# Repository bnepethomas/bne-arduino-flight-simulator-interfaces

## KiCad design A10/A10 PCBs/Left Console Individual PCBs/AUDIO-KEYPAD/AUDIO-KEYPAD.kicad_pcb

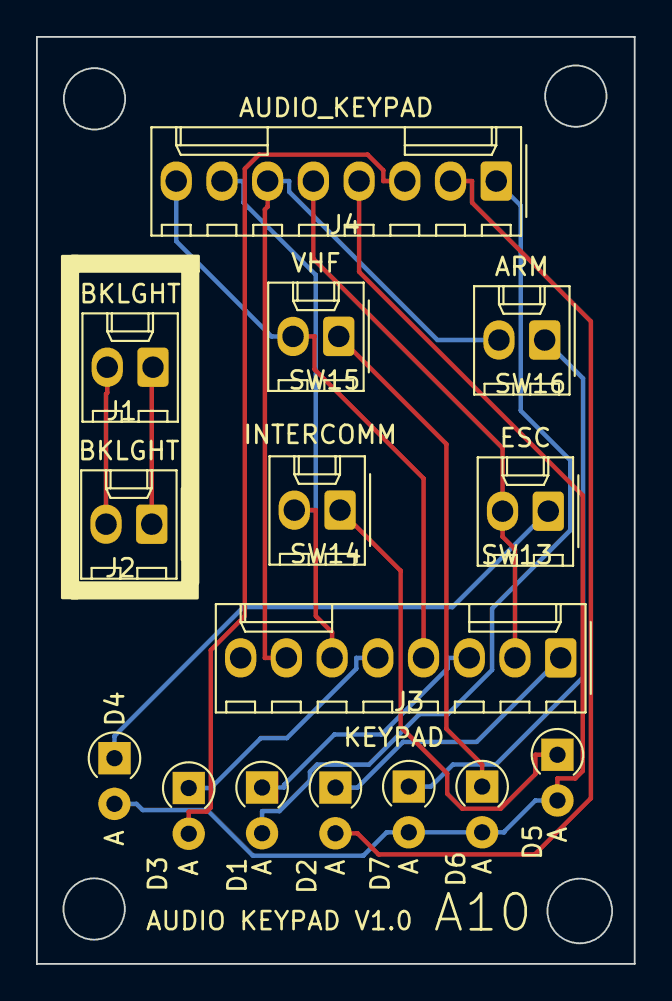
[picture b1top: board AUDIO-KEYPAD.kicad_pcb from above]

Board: 2 copper layers, 33.2 x 51.5 mm, 15 parts (0 on the bottom side), 17 nets.

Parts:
D1, D2, D3, D4, D5, D6, D7: D; D_A-405_P2.54mm_Vertical_AnodeUp
J1, J2: BKLGHT; Molex_KK-254_AE-6410-02A_1x02_P2.54mm_Vertical
J3: KEYPAD; Molex_KK-254_AE-6410-08A_1x08_P2.54mm_Vertical
J4: AUDIO_KEYPAD; Molex_KK-254_AE-6410-08A_1x08_P2.54mm_Vertical
SW13: ESC; Molex_KK-254_AE-6410-02A_1x02_P2.54mm_Vertical
SW14: INTERCOMM; Molex_KK-254_AE-6410-02A_1x02_P2.54mm_Vertical
SW15: VHF; Molex_KK-254_AE-6410-02A_1x02_P2.54mm_Vertical
SW16: ARM; Molex_KK-254_AE-6410-02A_1x02_P2.54mm_Vertical

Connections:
/COL0: D1.2 (A), J4.1
/COL0_POSTDIODE: D1.1 (K), J3.3
/COL1: D2.2 (A), J4.2
/COL1_POSTDIODE: D2.1 (K), J3.1
/COL2: D3.2 (A), J4.3
/COL2_POSTDIODE: D3.1 (K), J3.5
/COL3: D4.2 (A), D5.2 (A), D6.2 (A), D7.2 (A), J4.4
/ROW0: J3.2, J4.5, SW13.2
/ROW1: J3.7, J4.6, SW16.2
/ROW2: J3.6, J4.7, SW14.2
/ROW3: J3.4, J4.8, SW15.2
unnamed: D4.1 (K), SW13.1
unnamed: D5.1 (K), SW14.1
unnamed: D6.1 (K), SW15.1
unnamed: D7.1 (K), SW16.1
unnamed: J1.1, J2.1
unnamed: J1.2, J2.2

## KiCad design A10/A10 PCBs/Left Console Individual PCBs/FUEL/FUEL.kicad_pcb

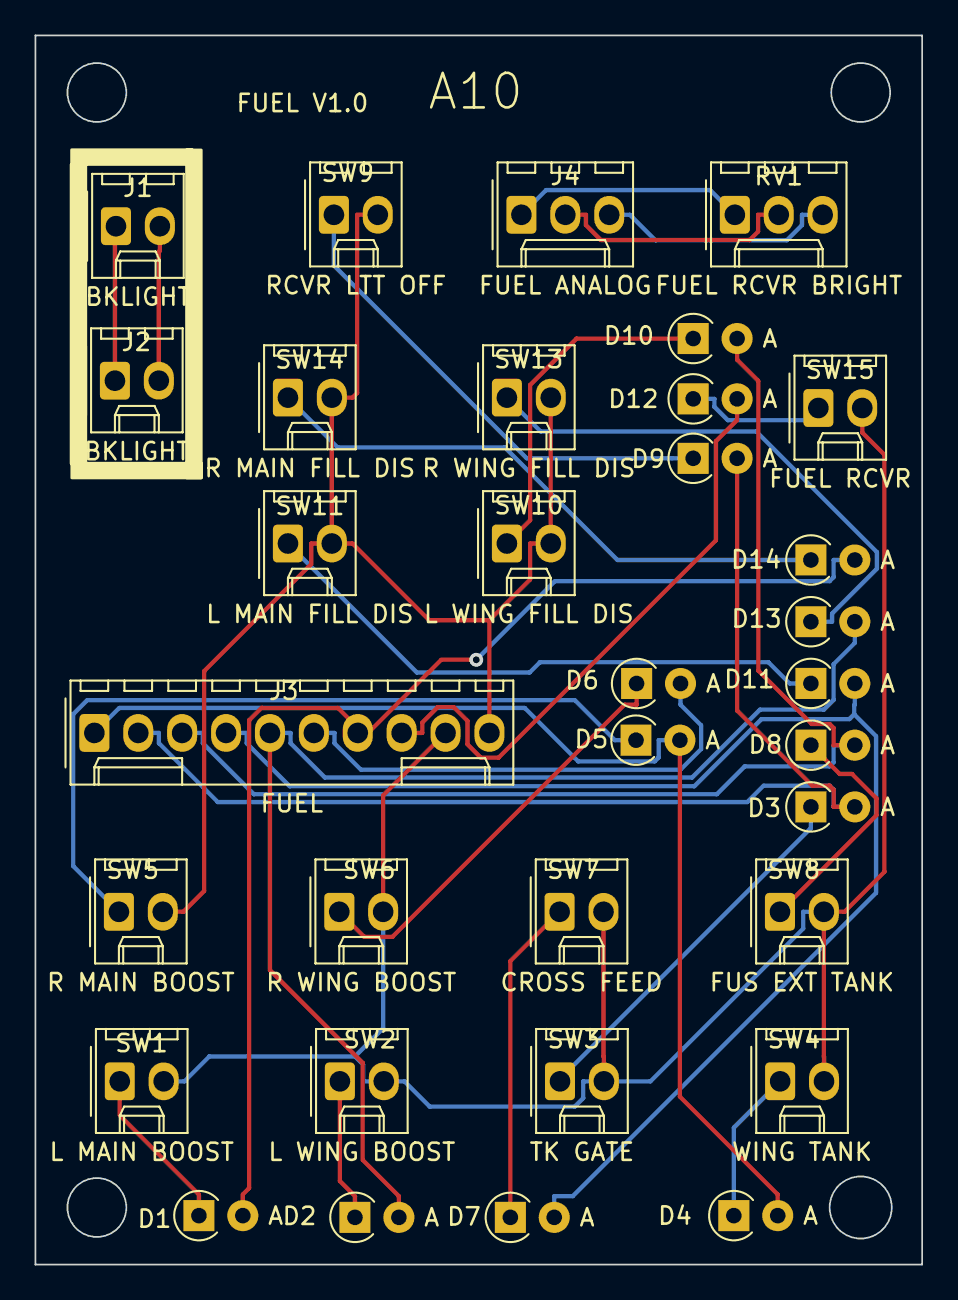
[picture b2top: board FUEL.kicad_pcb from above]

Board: 2 copper layers, 51.3 x 71.1 mm, 33 parts (0 on the bottom side), 29 nets.

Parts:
D1, D2, D3, D4, D5, D6, D7, D8, D9, D10, D11, D12, D13, D14: D; D_A-405_P2.54mm_Vertical_AnodeUp
J1, J2: BKLIGHT; Molex_KK-254_AE-6410-02A_1x02_P2.54mm_Vertical
J3: FUEL; Molex_KK-254_AE-6410-10A_1x10_P2.54mm_Vertical
J4: FUEL ANALOG; Molex_KK-254_AE-6410-03A_1x03_P2.54mm_Vertical
RV1: FUEL RCVR BRIGHT; Molex_KK-254_AE-6410-03A_1x03_P2.54mm_Vertical
SW1: L MAIN BOOST; Molex_KK-254_AE-6410-02A_1x02_P2.54mm_Vertical
SW2: L WING BOOST; Molex_KK-254_AE-6410-02A_1x02_P2.54mm_Vertical
SW3: TK GATE; Molex_KK-254_AE-6410-02A_1x02_P2.54mm_Vertical
SW4: WING TANK; Molex_KK-254_AE-6410-02A_1x02_P2.54mm_Vertical
SW5: R MAIN BOOST; Molex_KK-254_AE-6410-02A_1x02_P2.54mm_Vertical
SW6: R WING BOOST; Molex_KK-254_AE-6410-02A_1x02_P2.54mm_Vertical
SW7: CROSS FEED; Molex_KK-254_AE-6410-02A_1x02_P2.54mm_Vertical
SW8: FUS EXT TANK; Molex_KK-254_AE-6410-02A_1x02_P2.54mm_Vertical
SW9: RCVR LTT OFF; Molex_KK-254_AE-6410-02A_1x02_P2.54mm_Vertical
SW10: L WING FILL DIS; Molex_KK-254_AE-6410-02A_1x02_P2.54mm_Vertical
SW11: L MAIN FILL DIS; Molex_KK-254_AE-6410-02A_1x02_P2.54mm_Vertical
SW13: R WING FILL DIS; Molex_KK-254_AE-6410-02A_1x02_P2.54mm_Vertical
SW14: R MAIN FILL DIS; Molex_KK-254_AE-6410-02A_1x02_P2.54mm_Vertical
SW15: FUEL RCVR; Molex_KK-254_AE-6410-02A_1x02_P2.54mm_Vertical

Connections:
/ANALOG_5V: J4.1, RV1.1
/ANALOG_GND: J4.3, RV1.3
/COL0: D4.2 (A), D5.2 (A), J3.1
/COL1: D3.2 (A), D9.2 (A), J3.2
/COL2: D8.2 (A), D10.2 (A), J3.3
/COL3: D7.2 (A), D11.2 (A), J3.4
/COL4: D2.2 (A), D13.2 (A), J3.5
/COL5: D6.2 (A), J3.6
/COL6: D1.2 (A), D14.2 (A), J3.7
/COL7: D12.2 (A), J3.8
/RCVR_BRIGHT: J4.2, RV1.2
/ROW5: J3.9, SW1.2 (B), SW2.2 (B), SW3.2 (B), SW4.2 (B), SW6.2 (B), SW7.2 (B), SW8.2 (B), SW15.2 (B)
/ROW6: J3.10, SW5.2 (B), SW9.2 (B), SW10.2, SW11.2, SW13.2, SW14.2
unnamed: D1.1 (K), SW1.1 (A)
unnamed: D2.1 (K), SW2.1 (A)
unnamed: D3.1 (K), SW3.1 (A)
unnamed: D4.1 (K), SW4.1 (A)
unnamed: D5.1 (K), SW5.1 (A)
unnamed: D6.1 (K), SW6.1 (A)
unnamed: D7.1 (K), SW7.1 (A)
unnamed: D8.1 (K), SW8.1 (A)
unnamed: D9.1 (K), SW9.1 (A)
unnamed: D10.1 (K), SW10.1
unnamed: D11.1 (K), SW11.1
unnamed: D12.1 (K), SW15.1 (A)
unnamed: D13.1 (K), SW13.1
unnamed: D14.1 (K), SW14.1
unnamed: J1.1, J2.1
unnamed: J1.2, J2.2

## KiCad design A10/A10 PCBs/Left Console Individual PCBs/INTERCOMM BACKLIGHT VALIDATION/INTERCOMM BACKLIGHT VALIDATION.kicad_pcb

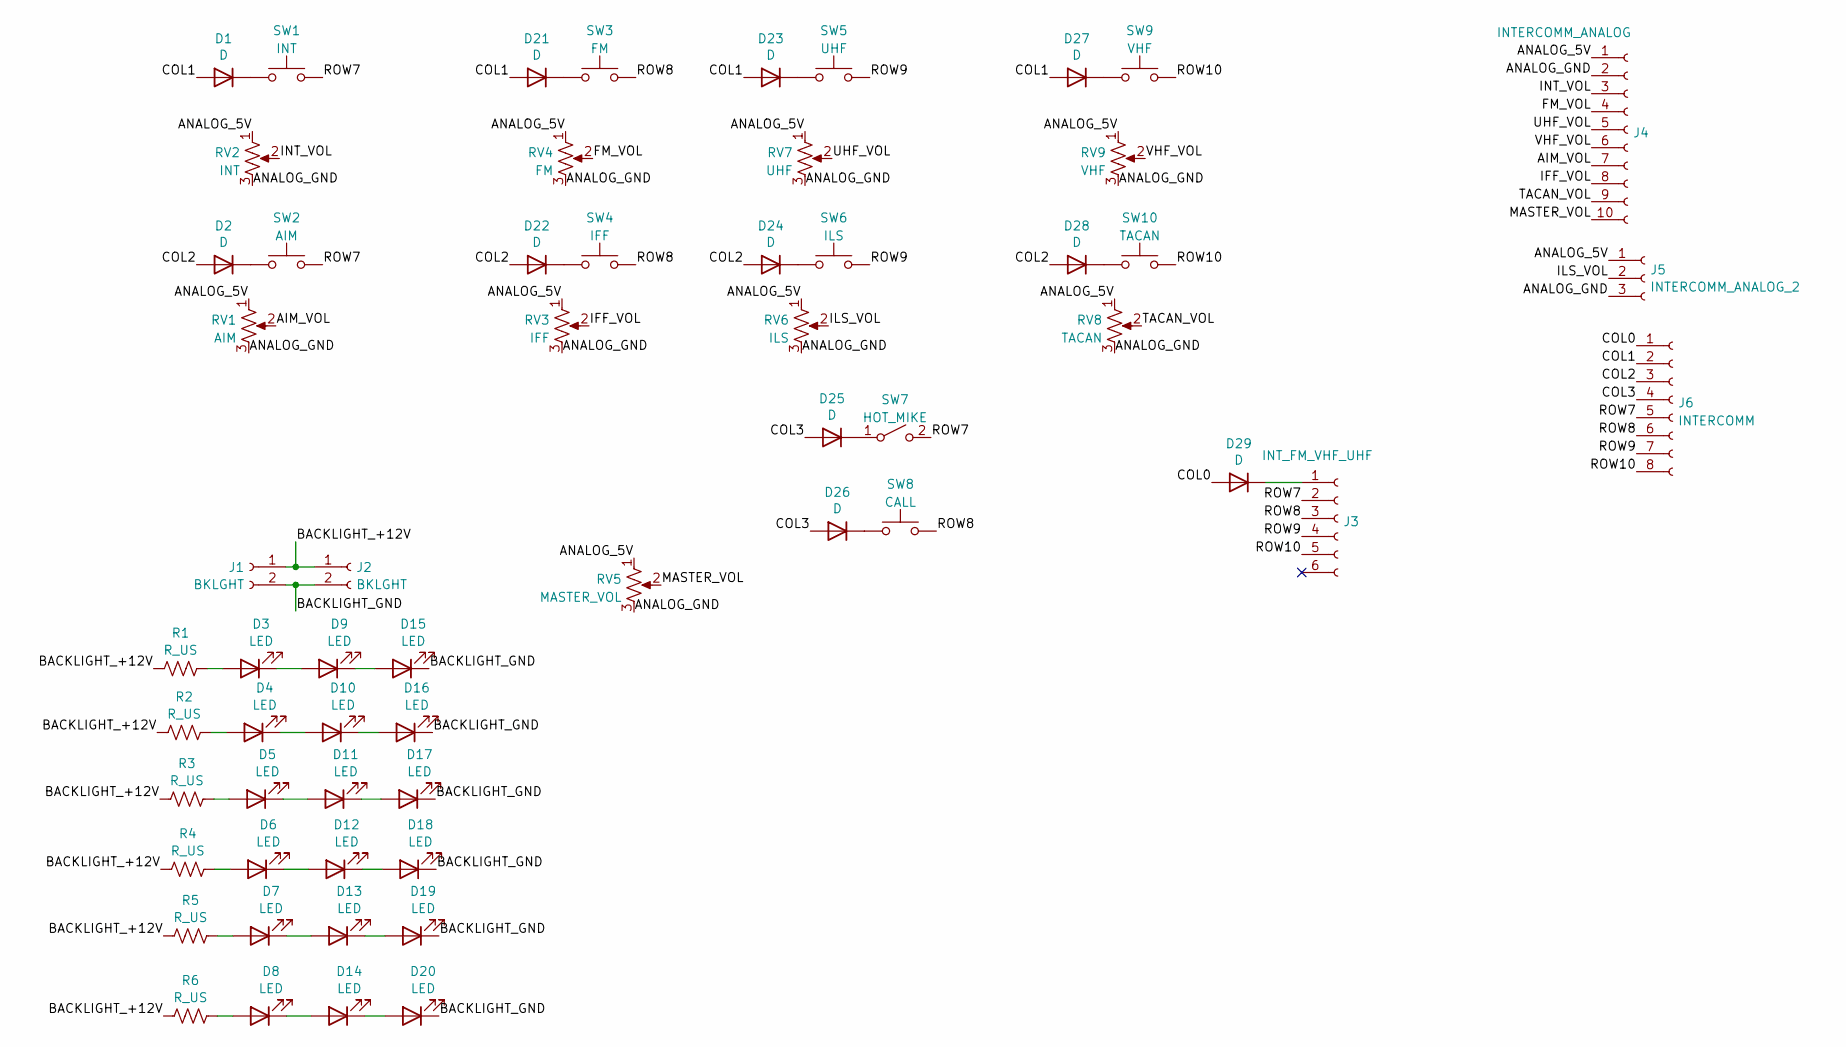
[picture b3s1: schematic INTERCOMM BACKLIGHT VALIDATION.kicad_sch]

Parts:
D1, D2, D21, D22, D23, D24, D25, D26, D27, D28, D29: D; D_A-405_P2.54mm_Vertical_AnodeUp
D3, D4, D5, D6, D7, D8, D9, D10, D11, D12, D13, D14, D15, D16, D17, D18, D19, D20: LED; LED_D3.0mm_FlatTop
J1, J2: BKLGHT; Molex_KK-254_AE-6410-02A_1x02_P2.54mm_Vertical
J3: INT_FM_VHF_UHF; Molex_KK-254_AE-6410-06A_1x06_P2.54mm_Vertical
J4: INTERCOMM_ANALOG; Molex_KK-254_AE-6410-10A_1x10_P2.54mm_Vertical
J5: INTERCOMM_ANALOG_2; Molex_KK-254_AE-6410-03A_1x03_P2.54mm_Vertical
J6: INTERCOMM; Molex_KK-254_AE-6410-08A_1x08_P2.54mm_Vertical
R1, R2, R3, R4, R5, R6: R_US; R_Axial_DIN0207_L6.3mm_D2.5mm_P2.54mm_Vertical
RV1: AIM; Molex_KK-254_AE-6410-03A_1x03_P2.54mm_Vertical
RV2: INT; Molex_KK-254_AE-6410-03A_1x03_P2.54mm_Vertical
RV3: IFF; Molex_KK-254_AE-6410-03A_1x03_P2.54mm_Vertical
RV4: FM; Molex_KK-254_AE-6410-03A_1x03_P2.54mm_Vertical
RV5: MASTER_VOL; Molex_KK-254_AE-6410-03A_1x03_P2.54mm_Vertical
RV6: ILS; Molex_KK-254_AE-6410-03A_1x03_P2.54mm_Vertical
RV7: UHF; Molex_KK-254_AE-6410-03A_1x03_P2.54mm_Vertical
RV8: TACAN; Molex_KK-254_AE-6410-03A_1x03_P2.54mm_Vertical
RV9: VHF; Molex_KK-254_AE-6410-03A_1x03_P2.54mm_Vertical
SW1: INT; Molex_KK-254_AE-6410-02A_1x02_P2.54mm_Vertical
SW2: AIM; Molex_KK-254_AE-6410-02A_1x02_P2.54mm_Vertical
SW3: FM; Molex_KK-254_AE-6410-02A_1x02_P2.54mm_Vertical
SW4: IFF; Molex_KK-254_AE-6410-02A_1x02_P2.54mm_Vertical
SW5: UHF; Molex_KK-254_AE-6410-02A_1x02_P2.54mm_Vertical
SW6: ILS; Molex_KK-254_AE-6410-02A_1x02_P2.54mm_Vertical
SW7: HOT_MIKE; Molex_KK-254_AE-6410-02A_1x02_P2.54mm_Vertical
SW8: CALL; Molex_KK-254_AE-6410-02A_1x02_P2.54mm_Vertical
SW9: VHF; Molex_KK-254_AE-6410-02A_1x02_P2.54mm_Vertical
SW10: TACAN; Molex_KK-254_AE-6410-02A_1x02_P2.54mm_Vertical

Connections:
/AIM_VOL: J4.7, RV1.2
/ANALOG_5V: J4.1, J5.1, RV1.1, RV2.1, RV3.1, RV4.1, RV5.1, RV6.1, RV7.1, RV8.1, RV9.1
/ANALOG_GND: J4.2, J5.3, RV1.3, RV2.3, RV3.3, RV4.3, RV5.3, RV6.3, RV7.3, RV8.3, RV9.3
/BACKLIGHT_+12V: J1.1, J2.1, R1.1, R2.1, R3.1, R4.1, R5.1, R6.1
/BACKLIGHT_GND: D15.1 (K), D16.1 (K), D17.1 (K), D18.1 (K), D19.1 (K), D20.1 (K), J1.2, J2.2
/COL0: D29.2 (A), J6.1
/COL1: D1.2 (A), D21.2 (A), D23.2 (A), D27.2 (A), J6.2
/COL2: D2.2 (A), D22.2 (A), D24.2 (A), D28.2 (A), J6.3
/COL3: D25.2 (A), D26.2 (A), J6.4
/FM_VOL: J4.4, RV4.2
/IFF_VOL: J4.8, RV3.2
/ILS_VOL: J5.2, RV6.2
/INT_VOL: J4.3, RV2.2
/MASTER_VOL: J4.10, RV5.2
/ROW7: J3.2, J6.5, SW1.2, SW2.2, SW7.2 (B)
/ROW8: J3.3, J6.6, SW3.2, SW4.2, SW8.2
/ROW9: J3.4, J6.7, SW5.2, SW6.2
/ROW10: J3.5, J6.8, SW9.2, SW10.2
/TACAN_VOL: J4.9, RV8.2
/UHF_VOL: J4.5, RV7.2
/VHF_VOL: J4.6, RV9.2
unnamed: D1.1 (K), SW1.1
unnamed: D2.1 (K), SW2.1
unnamed: D3.2 (A), R1.2
unnamed: D3.1 (K), D9.2 (A)
unnamed: D4.2 (A), R2.2
unnamed: D5.2 (A), R3.2
unnamed: D6.2 (A), R4.2
unnamed: D7.2 (A), R5.2
unnamed: D8.2 (A), R6.2
unnamed: D4.1 (K), D10.2 (A)
unnamed: D10.1 (K), D16.2 (A)
unnamed: D5.1 (K), D11.2 (A)
unnamed: D11.1 (K), D17.2 (A)
unnamed: D6.1 (K), D12.2 (A)
unnamed: D12.1 (K), D18.2 (A)
unnamed: D7.1 (K), D13.2 (A)
unnamed: D13.1 (K), D19.2 (A)
unnamed: D8.1 (K), D14.2 (A)
unnamed: D14.1 (K), D20.2 (A)
unnamed: D9.1 (K), D15.2 (A)
unnamed: D21.1 (K), SW3.1
unnamed: D22.1 (K), SW4.1
unnamed: D23.1 (K), SW5.1
unnamed: D24.1 (K), SW6.1
unnamed: D25.1 (K), SW7.1 (A)
unnamed: D26.1 (K), SW8.1
unnamed: D27.1 (K), SW9.1
unnamed: D28.1 (K), SW10.1
unnamed: D29.1 (K), J3.1

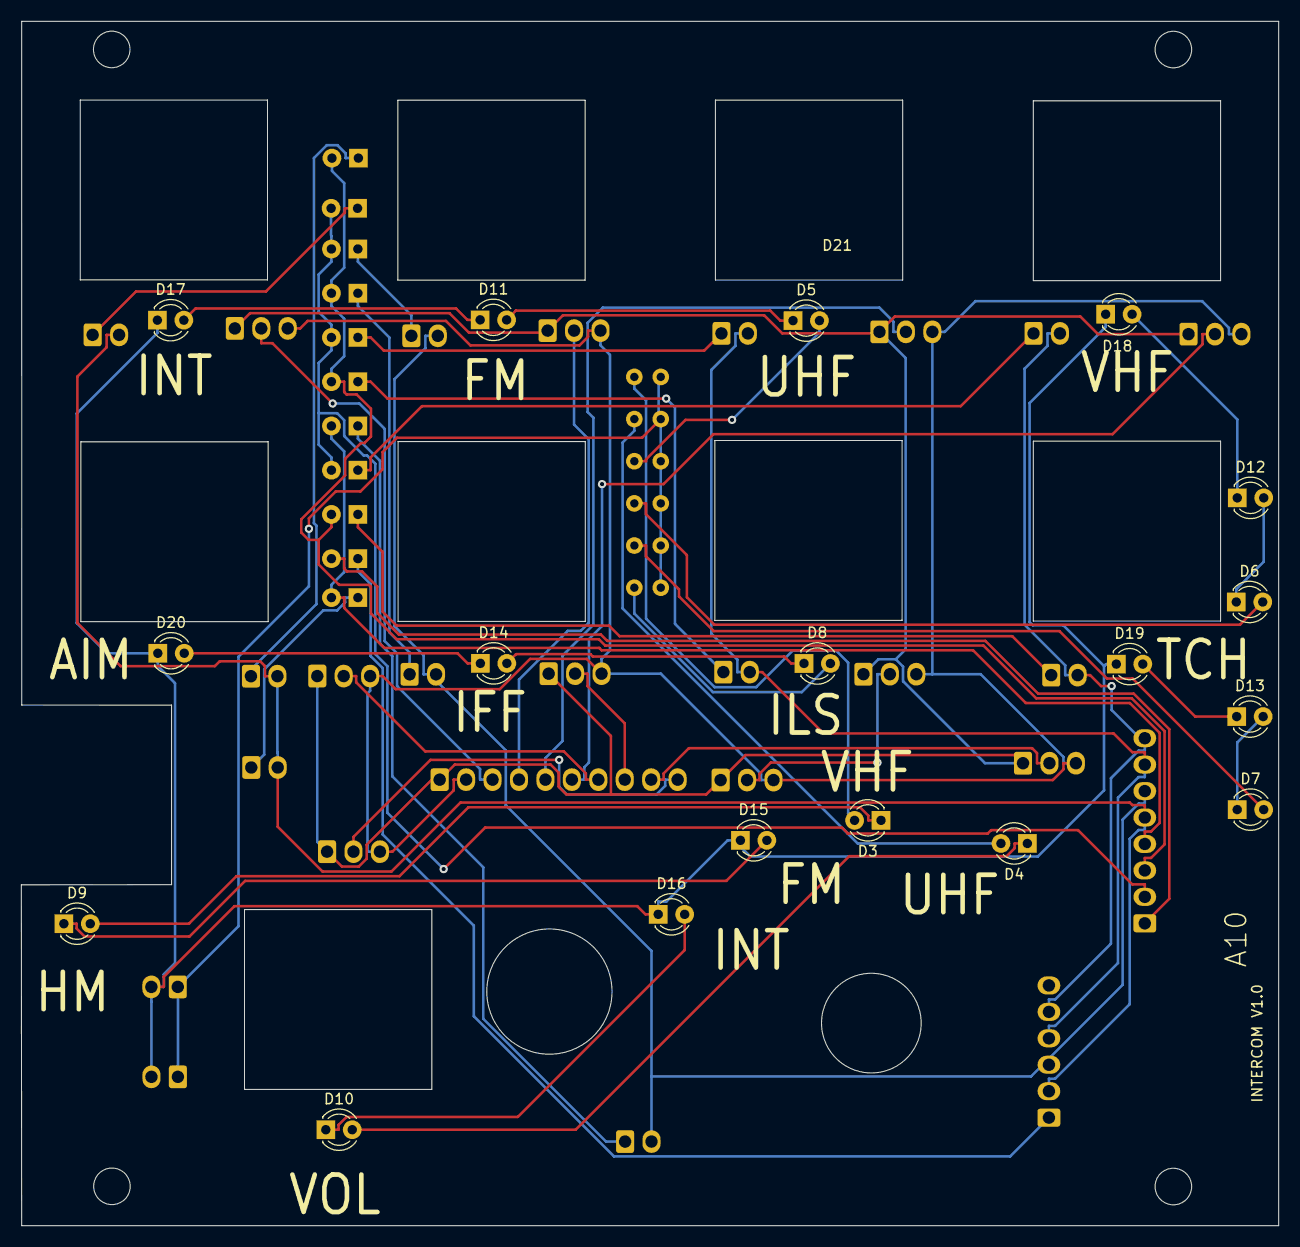
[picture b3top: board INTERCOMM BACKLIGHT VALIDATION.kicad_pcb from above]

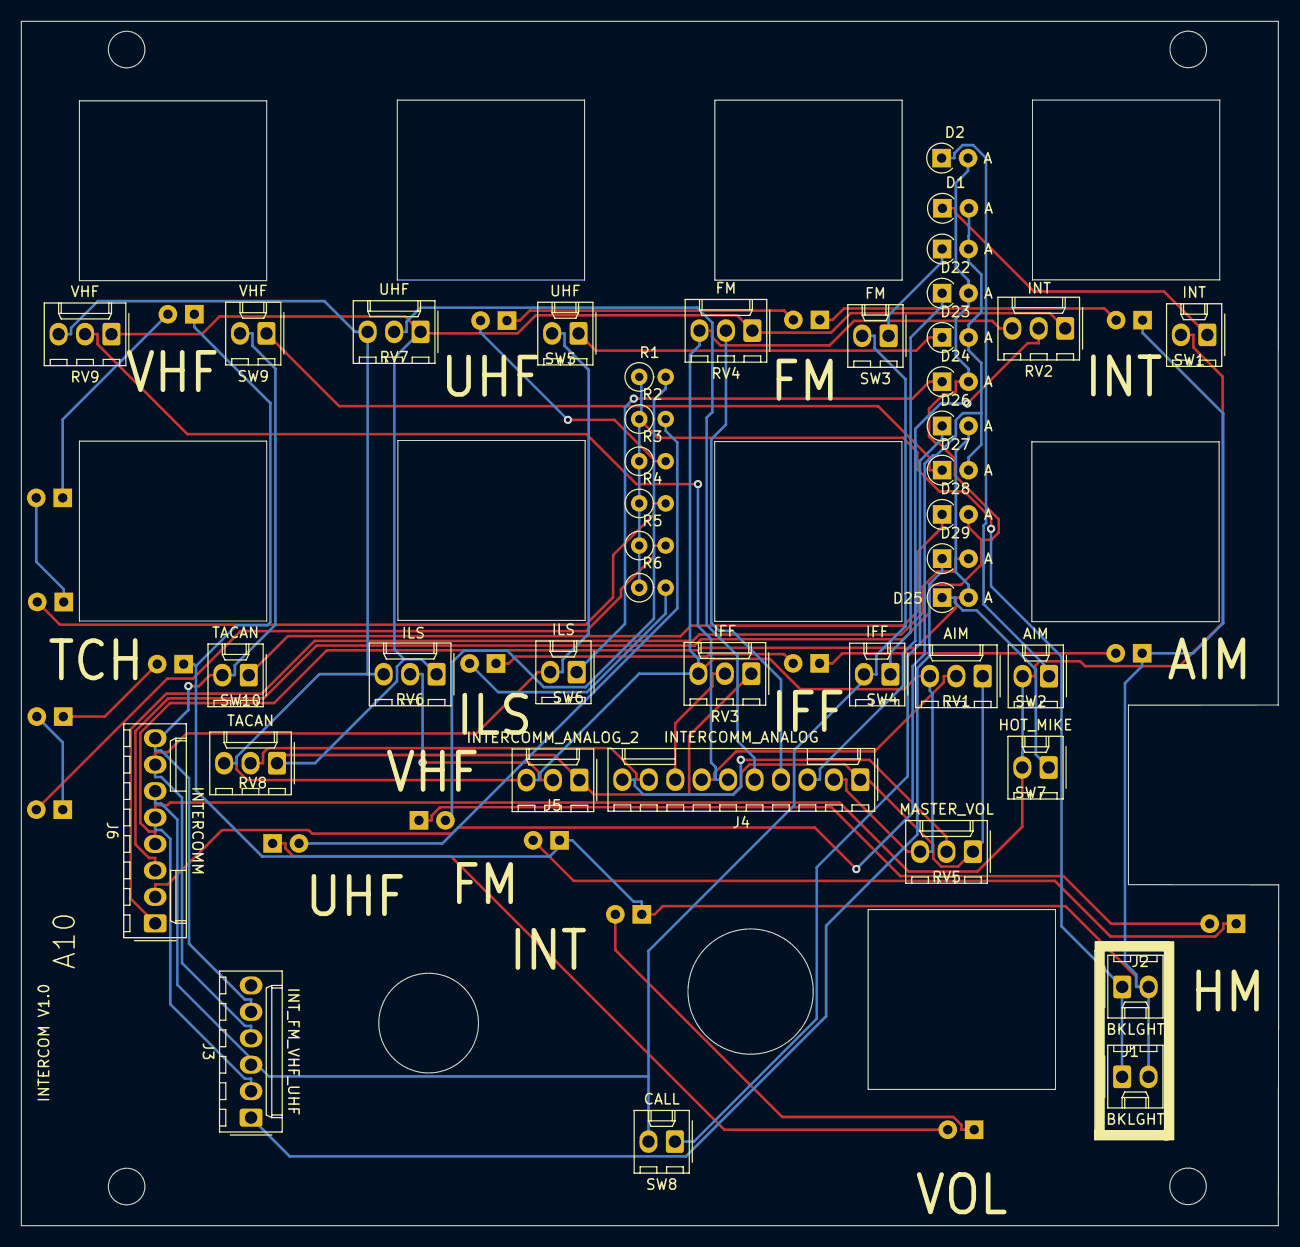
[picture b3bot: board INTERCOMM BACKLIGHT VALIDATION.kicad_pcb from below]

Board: 2 copper layers, 120.8 x 115.7 mm, 60 parts (42 on the bottom side), 50 nets.

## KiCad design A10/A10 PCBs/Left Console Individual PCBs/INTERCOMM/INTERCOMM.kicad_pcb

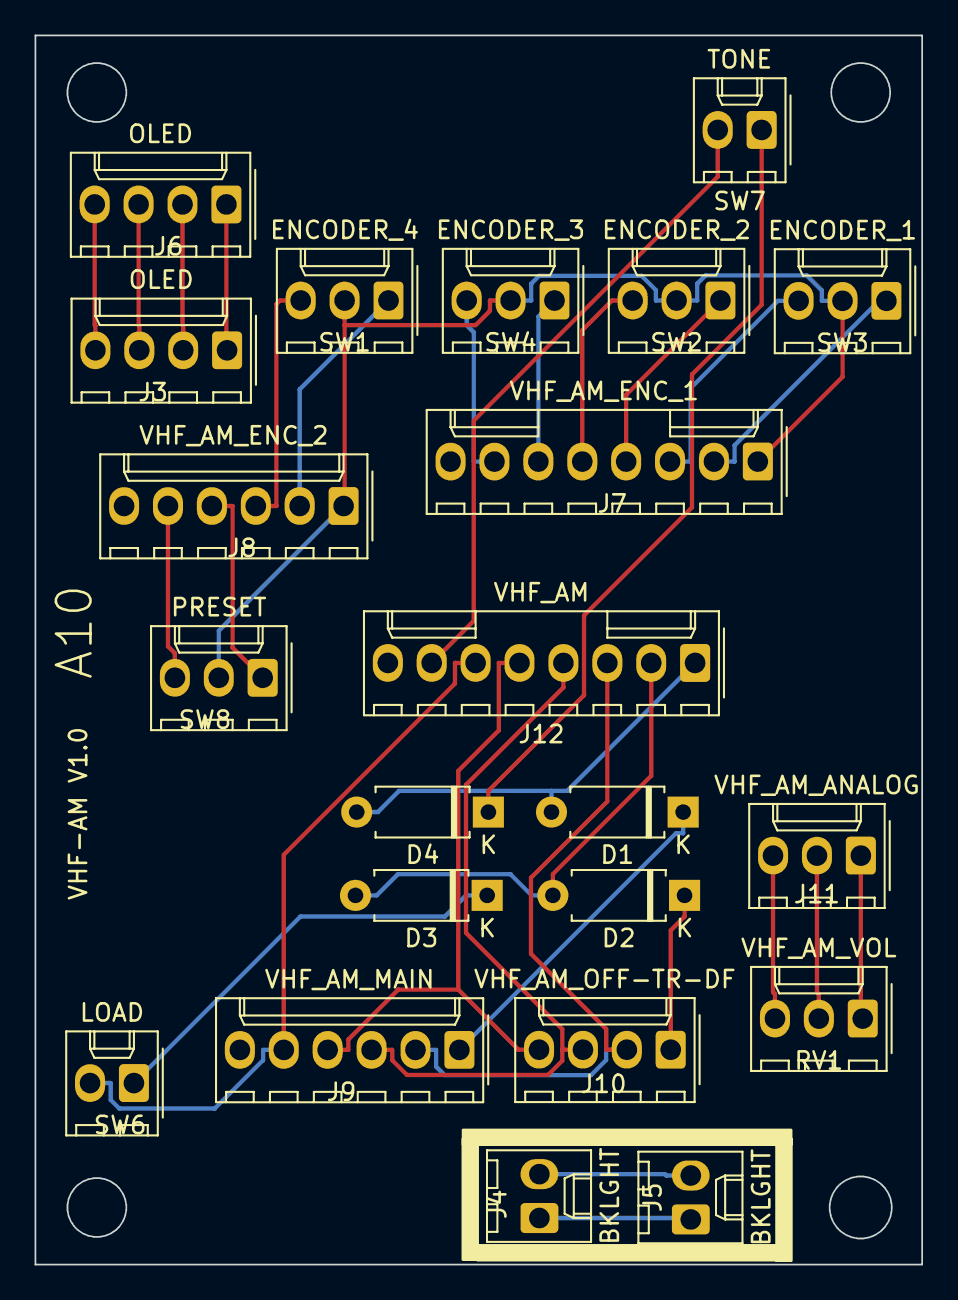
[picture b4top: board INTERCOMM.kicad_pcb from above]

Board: 2 copper layers, 51.3 x 71.1 mm, 22 parts (0 on the bottom side), 31 nets.

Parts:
D1, D2, D3, D4: D; D_A-405_P7.62mm_Horizontal
J3, J6: OLED; Molex_KK-254_AE-6410-04A_1x04_P2.54mm_Vertical
J4, J5: BKLGHT; Molex_KK-254_AE-6410-02A_1x02_P2.54mm_Vertical
J7: VHF_AM_ENC_1; Molex_KK-254_AE-6410-08A_1x08_P2.54mm_Vertical
J8: VHF_AM_ENC_2; Molex_KK-254_AE-6410-06A_1x06_P2.54mm_Vertical
J9: VHF_AM_MAIN; Molex_KK-254_AE-6410-06A_1x06_P2.54mm_Vertical
J10: VHF_AM_OFF-TR-DF; Molex_KK-254_AE-6410-04A_1x04_P2.54mm_Vertical
J11: VHF_AM_ANALOG; Molex_KK-254_AE-6410-03A_1x03_P2.54mm_Vertical
J12: VHF_AM; Molex_KK-254_AE-6410-08A_1x08_P2.54mm_Vertical
RV1: VHF_AM_VOL; Molex_KK-254_AE-6410-03A_1x03_P2.54mm_Vertical
SW1: ENCODER_4; Molex_KK-254_AE-6410-03A_1x03_P2.54mm_Vertical
SW2: ENCODER_2; Molex_KK-254_AE-6410-03A_1x03_P2.54mm_Vertical
SW3: ENCODER_1; Molex_KK-254_AE-6410-03A_1x03_P2.54mm_Vertical
SW4: ENCODER_3; Molex_KK-254_AE-6410-03A_1x03_P2.54mm_Vertical
SW6: LOAD; Molex_KK-254_AE-6410-02A_1x02_P2.54mm_Vertical
SW7: TONE; Molex_KK-254_AE-6410-02A_1x02_P2.54mm_Vertical
SW8: PRESET; Molex_KK-254_AE-6410-03A_1x03_P2.54mm_Vertical

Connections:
/ANALOG_5V: J11.1, RV1.1
/ANALOG_GND: J11.3, RV1.3
/COL4: D1.2 (A), D4.2 (A), J12.1
/COL5: D2.2 (A), D3.2 (A), J12.2
/ROW0: J9.2, J10.2, J12.3
/ROW1: J9.3, J10.3, J12.4
/ROW2: J9.4, J10.4, J12.5
/ROW3: J9.5, J12.6, SW6.2
/ROW4: J12.7, SW7.2
/VHF_AM_VOL: J11.2, RV1.2
/VHF__AM_ENC_1_A: J7.2, SW3.1
/VHF__AM_ENC_1_B: J7.3, SW3.3
/VHF__AM_ENC_2_A: J7.4, SW2.1
/VHF__AM_ENC_2_B: J7.5, SW2.3
/VHF__AM_ENC_3_A: J7.6, SW4.1
/VHF__AM_ENC_3_B: J7.7, SW4.3
/VHF__AM_ENC_4_A: J8.2, SW1.1
/VHF__AM_ENC_4_B: J8.3, SW1.3
/VHF__AM_PRESET_A: J8.4, SW8.1
/VHF__AM_PRESET_B: J8.5, SW8.3
GND: J7.1, J8.1, SW1.2, SW2.2, SW3.2, SW4.2, SW8.2
unnamed: D1.1 (K), J9.1
unnamed: D2.1 (K), J10.1
unnamed: D3.1 (K), SW6.1
unnamed: D4.1 (K), SW7.1
unnamed: J3.1, J6.1
unnamed: J3.2, J6.2
unnamed: J3.3, J6.3
unnamed: J3.4, J6.4
unnamed: J4.1, J5.1
unnamed: J4.2, J5.2

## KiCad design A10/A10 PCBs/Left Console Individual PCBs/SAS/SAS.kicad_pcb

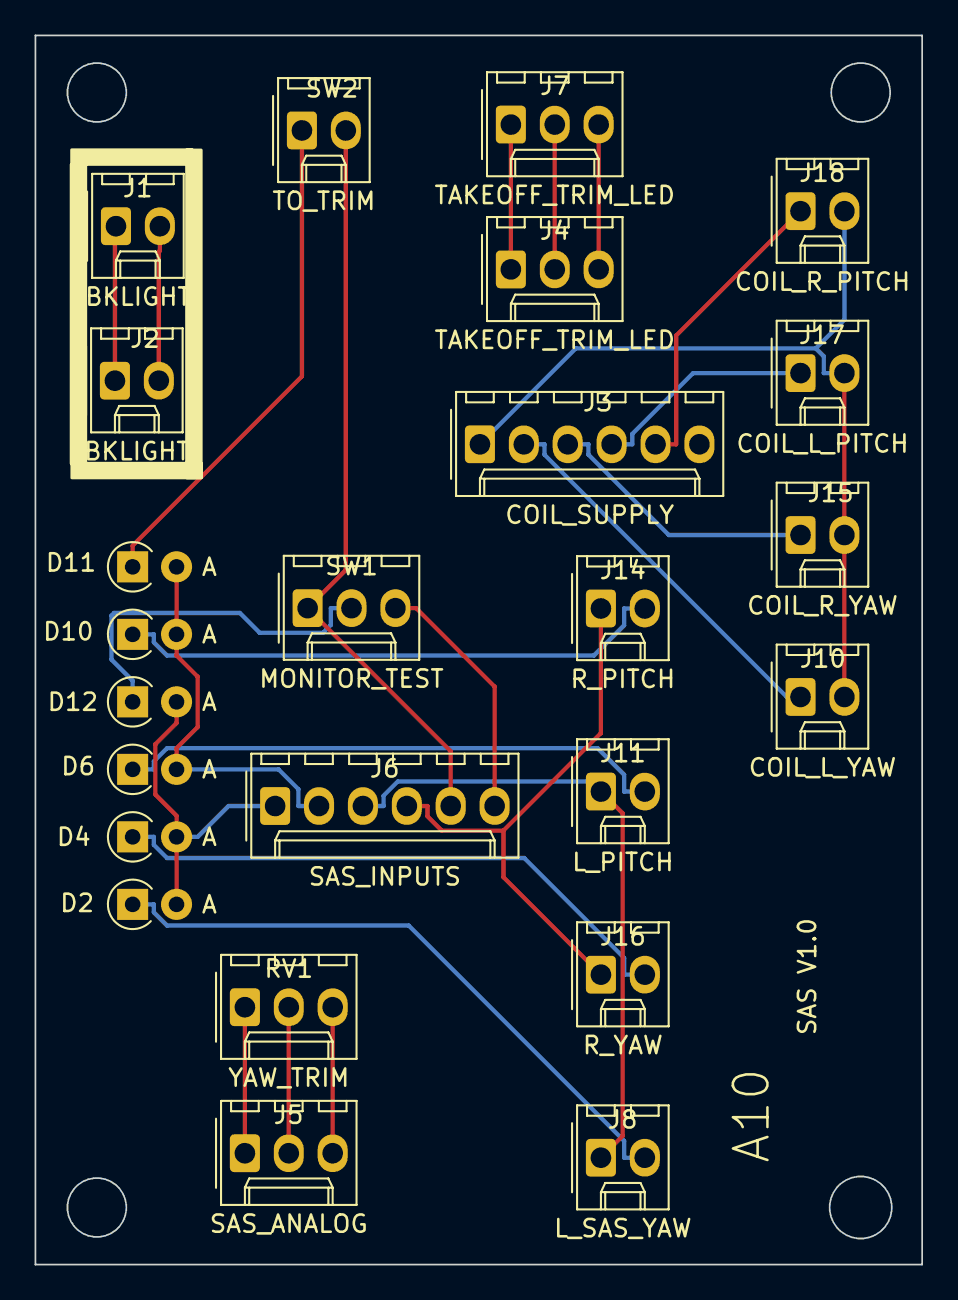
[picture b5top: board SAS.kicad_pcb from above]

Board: 2 copper layers, 51.3 x 71.1 mm, 24 parts (0 on the bottom side), 25 nets.

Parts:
D2, D4, D6, D10, D11, D12: D; D_A-405_P2.54mm_Vertical_AnodeUp
J1, J2: BKLIGHT; Molex_KK-254_AE-6410-02A_1x02_P2.54mm_Vertical
J3: COIL_SUPPLY; Molex_KK-254_AE-6410-06A_1x06_P2.54mm_Vertical
J4, J7: TAKEOFF_TRIM_LED; Molex_KK-254_AE-6410-03A_1x03_P2.54mm_Vertical
J5: SAS_ANALOG; Molex_KK-254_AE-6410-03A_1x03_P2.54mm_Vertical
J6: SAS_INPUTS; Molex_KK-254_AE-6410-06A_1x06_P2.54mm_Vertical
J8: L_SAS_YAW; Molex_KK-254_AE-6410-02A_1x02_P2.54mm_Vertical
J10: COIL_L_YAW; Molex_KK-254_AE-6410-02A_1x02_P2.54mm_Vertical
J11: L_PITCH; Molex_KK-254_AE-6410-02A_1x02_P2.54mm_Vertical
J14: R_PITCH; Molex_KK-254_AE-6410-02A_1x02_P2.54mm_Vertical
J15: COIL_R_YAW; Molex_KK-254_AE-6410-02A_1x02_P2.54mm_Vertical
J16: R_YAW; Molex_KK-254_AE-6410-02A_1x02_P2.54mm_Vertical
J17: COIL_L_PITCH; Molex_KK-254_AE-6410-02A_1x02_P2.54mm_Vertical
J18: COIL_R_PITCH; Molex_KK-254_AE-6410-02A_1x02_P2.54mm_Vertical
RV1: YAW_TRIM; Molex_KK-254_AE-6410-03A_1x03_P2.54mm_Vertical
SW1: MONITOR_TEST; Molex_KK-254_AE-6410-03A_1x03_P2.54mm_Vertical
SW2: TO_TRIM; Molex_KK-254_AE-6410-02A_1x02_P2.54mm_Vertical

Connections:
/ANALOG_5V: J5.1, RV1.1
/ANALOG_GND: J5.3, RV1.3
/COIL_28V: J3.1, J10.2, J15.2, J17.2, J18.2
/COIL_L_PITCH: J3.4, J17.1
/COIL_L_YAW: J3.2, J10.1
/COIL_R_PITCH: J3.5, J18.1
/COIL_R_YAW: J3.3, J15.1
/COL9: D2.2 (A), D4.2 (A), D12.2 (A), J6.1
/COL10: D6.2 (A), D10.2 (A), D11.2 (A), J6.2
/ROW0: J6.3, J8.1, J11.1
/ROW1: J6.4, J14.1, J16.1
/ROW2: J6.5, SW1.1, SW2.2
/ROW3: J6.6, SW1.3
/YAW_TRIM: J5.2, RV1.2
unnamed: D2.1 (K), J8.2
unnamed: D4.1 (K), J16.2
unnamed: D6.1 (K), J11.2
unnamed: D10.1 (K), J14.2
unnamed: D11.1 (K), SW2.1
unnamed: D12.1 (K), SW1.2
unnamed: J1.1, J2.1
unnamed: J1.2, J2.2
unnamed: J4.1, J7.1
unnamed: J4.2, J7.2
unnamed: J4.3, J7.3

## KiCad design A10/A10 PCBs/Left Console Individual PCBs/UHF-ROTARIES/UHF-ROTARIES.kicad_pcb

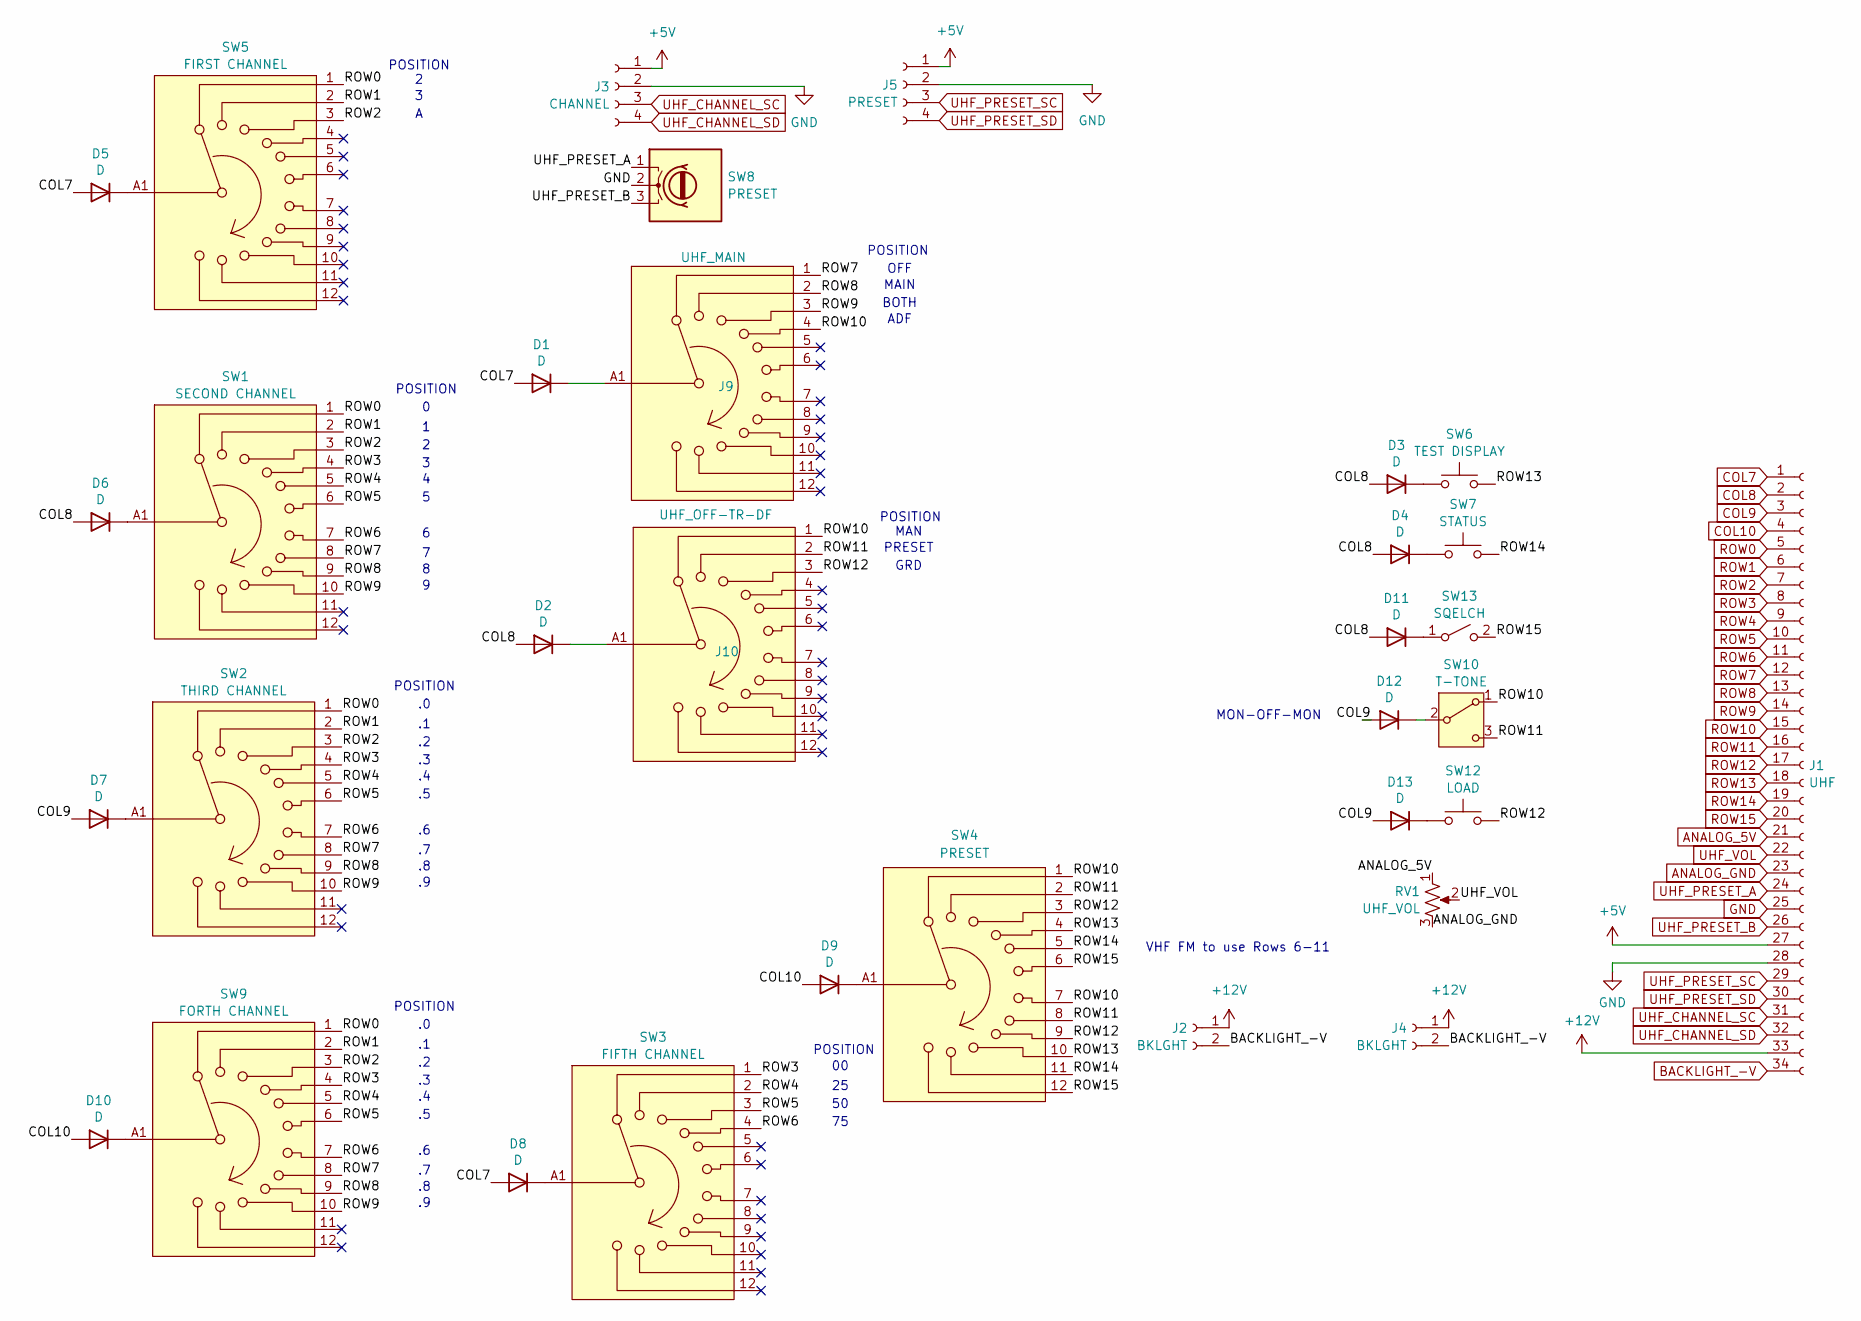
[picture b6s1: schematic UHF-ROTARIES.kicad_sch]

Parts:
D1, D2, D3, D4, D5, D6, D7, D8, D9, D10, D11, D12, D13: D; D_A-405_P7.62mm_Horizontal
J1: UHF; IDC-Header_2x17_P2.54mm_Vertical
J2, J4: BKLGHT; JST_XH_B2B-XH-A_1x02_P2.50mm_Vertical
J3: CHANNEL; JST_XH_B4B-XH-A_1x04_P2.50mm_Vertical
J5: PRESET; JST_XH_B4B-XH-A_1x04_P2.50mm_Vertical
J9: UHF_MAIN; ALPHA 12 POS
J10: UHF_OFF-TR-DF; ALPHA 12 POS
RV1: UHF_VOL; JST_XH_B3B-XH-A_1x03_P2.50mm_Vertical
SW1: SECOND CHANNEL; ALPHA 12 POS
SW2: THIRD CHANNEL; ALPHA 12 POS
SW3: FIFTH CHANNEL; ALPHA 12 POS
SW4: PRESET; ALPHA 12 POS
SW5: FIRST CHANNEL; ALPHA 12 POS
SW6: TEST DISPLAY; JST_XH_B2B-XH-A_1x02_P2.50mm_Vertical
SW7: STATUS; JST_XH_B2B-XH-A_1x02_P2.50mm_Vertical
SW8: PRESET; JST_XH_B3B-XH-A_1x03_P2.50mm_Vertical
SW9: FORTH CHANNEL; ALPHA 12 POS
SW10: T-TONE; JST_XH_B3B-XH-A_1x03_P2.50mm_Vertical
SW12: LOAD; JST_XH_B2B-XH-A_1x02_P2.50mm_Vertical
SW13: SQELCH; JST_XH_B2B-XH-A_1x02_P2.50mm_Vertical

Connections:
+5V: J1.27, J3.1, J5.1
+12V: J1.33, J2.1, J4.1
ANALOG_5V: J1.21, RV1.1
ANALOG_GND: J1.23, RV1.3
BACKLIGHT_-V: J1.34, J2.2, J4.2
COL7: D1.2 (A), D5.2 (A), D8.2 (A), J1.1
COL8: D2.2 (A), D3.2 (A), D4.2 (A), D6.2 (A), D11.2 (A), J1.2
COL9: D7.2 (A), D12.2 (A), D13.2 (A), J1.3
COL10: D9.2 (A), D10.2 (A), J1.4
GND: J1.25, J1.28, J3.2, J5.2, SW8.2
unnamed: D1.1 (K), J9.A1
unnamed: D2.1 (K), J10.A1
unnamed: D3.1 (K), SW6.1
unnamed: D4.1 (K), SW7.1
unnamed: D5.1 (K), SW5.A1
unnamed: D6.1 (K), SW1.A1
unnamed: D7.1 (K), SW2.A1
unnamed: D8.1 (K), SW3.A1
unnamed: D9.1 (K), SW4.A1
unnamed: D10.1 (K), SW9.A1
unnamed: D11.1 (K), SW13.1 (A)
unnamed: D12.1 (K), SW10.2 (B)
unnamed: D13.1 (K), SW12.1
ROW0: J1.5, SW1.1, SW2.1, SW5.1, SW9.1
ROW1: J1.6, SW1.2, SW2.2, SW5.2, SW9.2
ROW2: J1.7, SW1.3, SW2.3, SW5.3, SW9.3
ROW3: J1.8, SW1.4, SW2.4, SW3.1, SW9.4
ROW4: J1.9, SW1.5, SW2.5, SW3.2, SW9.5
ROW5: J1.10, SW1.6, SW2.6, SW3.3, SW9.6
ROW6: J1.11, SW1.7, SW2.7, SW3.4, SW9.7
ROW7: J1.12, J9.1, SW1.8, SW2.8, SW9.8
ROW8: J1.13, J9.2, SW1.9, SW2.9, SW9.9
ROW9: J1.14, J9.3, SW1.10, SW2.10, SW9.10
ROW10: J1.15, J9.4, J10.1, SW4.1, SW4.7, SW10.1 (A)
ROW11: J1.16, J10.2, SW4.2, SW4.8, SW10.3 (C)
ROW12: J1.17, J10.3, SW4.3, SW4.9, SW12.2
ROW13: J1.18, SW4.4, SW4.10, SW6.2
ROW14: J1.19, SW4.5, SW4.11, SW7.2
ROW15: J1.20, SW4.6, SW4.12, SW13.2 (B)
UHF_CHANNEL_SC: J1.31, J3.3
UHF_CHANNEL_SD: J1.32, J3.4
UHF_PRESET_A: J1.24, SW8.1
UHF_PRESET_B: J1.26, SW8.3
UHF_PRESET_SC: J1.29, J5.3
UHF_PRESET_SD: J1.30, J5.4
UHF_VOL: J1.22, RV1.2

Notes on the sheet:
MAIN
GRD
VHF FM to use Rows 6-11
POSITION
OFF
ADF
MON-OFF-MON
PRESET
BOTH
MAN
